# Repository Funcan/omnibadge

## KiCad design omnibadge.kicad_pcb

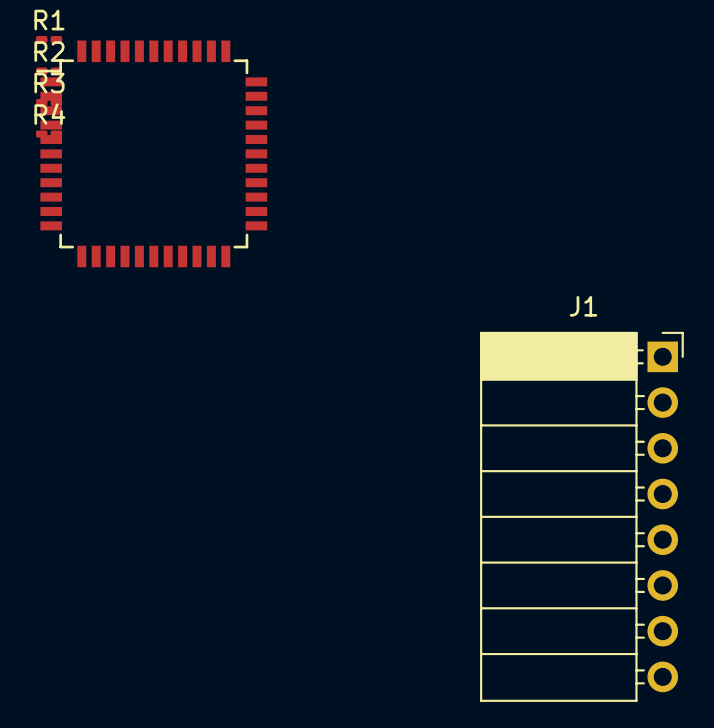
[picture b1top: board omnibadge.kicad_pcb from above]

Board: 2 copper layers, 6 parts (0 on the bottom side), 14 nets, no tracks yet.

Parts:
J1: Conn_01x08_Socket; PinSocket_1x08_P2.54mm_Horizontal
R1, R2: 4k7; R_0201_0603Metric_Pad0.64x0.40mm_HandSolder
R3, R4: 2k2; R_0201_0603Metric_Pad0.64x0.40mm_HandSolder
U1: LQFP44_Tight

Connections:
+3.3V: R2.1, R3.1, U1.14 (STB), U1.31 (X0), U1.38 (VDD)
GND: R1.2, R4.2, U1.10 (P/_S), U1.12 (VSS), U1.18 (AX1), U1.19 (AX2), U1.20 (AY0), U1.21 (AY1), U1.30 (X1), U1.40 (AY2), U1.42 (AX3), U1.43 (AX0)
IO0: J1.1, U1.33 (Y0)
IO1: J1.2, U1.35 (Y1)
IO2: J1.3, U1.37 (Y2)
IO3: J1.4, U1.39 (Y3)
IO4: J1.5, U1.17 (Y4)
IO5: J1.6, U1.15 (Y5)
IO6: J1.7, U1.13 (Y6)
IO7: J1.8, U1.11 (Y7)
unnamed: R3.2, U1.27 (X4)
unnamed: R4.1, U1.26 (X5)
unnamed: R2.2, U1.25 (X12)
unnamed: R1.1, U1.24 (X13)

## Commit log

2024-05-06 First pass at schematic
    Missing footprints for the joystick and screen currently, having trouble
    with the libraries
